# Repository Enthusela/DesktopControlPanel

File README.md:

# The Desktop Control Panel Project

An open-source, hand-built, tactile, home-brew smart-home hub with analog PC audio monitoring and control.

## Features

* ARGB LED device control with HSV and color-temperature control modes
* App-based volume mixing in Windows, including OS/Game/Discord channels
* Motorised knobs enable multiple control modes on a single set of inputs
* Mains power control: Toggle switches control mains power to the PC, monitors, and speakers via rental-safe RF-based remote-control mains outlets.
* Analog audio monitoring: PC soundcard connects to VU meters and IN-9 Nixie Tubes for level and 3-band spectrum monitoring, respectively
* Moog-inspired build quality: wood cabinet, black brushed-aluminium faceplate, big, satisfying switchgear, and actual Moog knobs/rockers because why not.
* "Seamless" E-ink display: White-on-black E-ink panel creates a non-light-emitting display integrated into the non-light-emitting faceplate.
* Integrated website: the website for this Control Panel project is hosted on the Raspberry Pi running inside the Control Panel
* Integration with Home Assistant for ARGB room-lighting via ESP Wifi boards
* Automatic Temperature-based color control: automatically transition room lighting from cool to warm as the sun sets here in Perth, Western Australia.
* Homebrew phone-control app: Home Assistant has this, of course, but this sounded like a good excuse to learn React Native.

<details>
<summary>Feature Development Status Table</summary>

| Feature/Pipeline                      | Order In Pipeline | Sub-function                        | Status |
|:--------------------------------------|:---:|:----------------------------------------------------|:-----|
| Faceplate -> Mega Hardware Pipeline   | 1   | Faceplate Input Hardware                            | Done |
| Faceplate -> Mega Hardware Pipeline   | 2   | Faceplate Input Breakout Board                      | Testing |
| Faceplate -> Mega Hardware Pipeline   | 3   | Mega* Input Shield                                  | Testing |
| Mega -> Raspi Hardware Pipeline       | 1   | USB Connection                                      | Done |
| Raspi -> Uno Hardware Pipeline        | 1   | USB Connection                                      | Done |
| Raspi -> PC Hardware Pipeline         | 1   | Local Wifi Connection                               | Done |
| Input Knob Motorisation               | 1   | Mega Programming - Input Knob Control Modes         | Done |
| Input Knob Motorisation               | 2   | Motor Driver Shield                                 | Done |
| Input Knob Motorisation               | 3   | Shield -> Motor Connection                          | Done | 
| PC ARGB Control                       | 1   | Mega Programming - Input signal processing          | Done |
| PC ARGB Control                       | 2a  | Raspi* Programming - Input passthrough to Uno       | Done |
| PC ARGB Control                       | 2b  | Raspi Programming - Home Assistant/Web App          | Not Started |
| PC ARGB Control                       | 3a  | Uno* Programming - Manual HSV-based Color Control   | Done |
| PC ARGB Control                       | 3b  | Uno Programming - Manual Temp-based Color Control   | Done |
| PC ARGB Control                       | 3c  | Uno Programming - Auto Temp-based Color Control     | Not Started |
| PC ARGB Control                       | 4   | Uno ARGB Breakout Shield                            | To Be Ordered |
| PC ARGB Control                       | 5   | PC ARGB Devices                                     | Done |
| PC Volume Control                     | 1   | Raspi Programming - Input passthrough to PC         | Done |
| PC Volume Control                     | 2a  | PC Programming - Main Volume Control                | Done |
| PC Volume Control                     | 2b  | PC Programming - Three-channel App Volume Control   | Done |
| PC Volume Control                     | 2c  | PC Programming - Audio Output Device Selection      | Done |
| Mains Power Control                   | 1   | Mega Programming - Input Signal Processing          | In progress |
| Mains Power Control                   | 2   | Mega -> RF PCB Breakout Board                       | In progress |
| Mains Power Control                   | 3   | RF PCB -> Remote Mains Outlet Connection            | In progress |
| Mains Power Control                   | 4   | Remote Mains Outlets - Test Working                 | In progress |
| PC Audio Level Meters                 | 1   | Soundcard TRS Output Levels                         | Done |
| PC Audio Level Meters                 | 2a  | Soundcard -> Driver Board Connection                | Done |
| PC Audio Level Meters                 | 2b  | Power Supply -> Driver Board Connection             | Developing |
| PC Audio Level Meters                 | 3   | VU Meter Driver Board                               | Done |
| PC Audio Level Meters                 | 4a  | VU Meter Level Outputs                              | Done |
| PC Audio Level Meters                 | 4b  | VU Meter LED Outputs                                | Done |
| PC Audio Level Meters                 | 5a  | VU Meters                                           | Done |
| PC Audio Level Meters                 | 5b  | VU Meter LEDs                                       | Prototyped |
| PC Audio Spectrum Analyser            | 1   | Soundcard Optical Output Levels                     | Done |
| PC Audio Spectrum Analyser            | 2   | Soundcard -> Digital I/O Board Connection           | Done |
| PC Audio Spectrum Analyser            | 3   | Raspberry Pi Digital Audio I/O Board                | Testing |
| PC Audio Spectrum Analyser            | 4   | Raspberry Pi Digital Audio I/O Processing           | Developing |
| PC Audio Spectrum Analyser            | 5   | Custom Nixie Tube Driver HAT                        | Developing |
| PC Audio Spectrum Analyser            | 6   | Driver HAT -> Nixie Tube Connection                 | Done |
| PC Audio Spectrum Analyser            | 7   | Power Supply to Driver Board                        | Developing |
| e-Ink Display                         | 1   | Raspberry Pi Programming - Image Output             | Developing |
| e-Ink Display                         | 2   | Raspberry Pi HAT                                    | Done |
| e-Ink Display                         | 3   | e-Ink Display                                       | Done |
| Project Website                       | 1   | Proxy Server (nginx)                                | Done |
| Project Website                       | 2   | Domain Hosting                                      | Done |
| Project Website                       | 3   | Server (node.js)                                    | Done |
| Project Website                       | 4a  | Homepage                                            | In progress |
| Project Website                       | 4b  | Brief                                               | In progress |
| Project Website                       | 4c  | Timeline                                            | In progress |
| Project Website                       | 4d  | Parts List                                          | In progress |
| Project Website                       | 4e  | Gallery                                             | In progress |
| Project Website                       | 4f  | Interactive Panel Map                               | Not started |
| Cabinet                               | N/A | Faceplate VU Meter Mounts                           | Done |
| Cabinet                               | N/A | Faceplate Nixie Tube Mounts                         | Done |
| Cabinet                               | N/A | Faceplate Soundcard Mount                           | Done |
| Cabinet                               | N/A | Faceplate e-Ink Display Mount                       | Done |
| Cabinet                               | N/A | Faceplate Input Knobs                               | Done |
| Cabinet                               | N/A | Faceplate Input Knob Motors/Gears                   | Done |
| Cabinet                               | N/A | Faceplate Input Rocker Switches                     | Done |
| Cabinet                               | N/A | Faceplate Input Toggle Switches                     | Done |
| Cabinet                               | N/A | Faceplate Input Push-button Switches                | Done |
| Cabinet                               | N/A | Internal Mounting Plate                             | Done |
| Cabinet                               | N/A | Rear Plate Plate                                    | Done |
| Cabinet                               | N/A | Cabinet Top Plate                                   | Done |
| Cabinet                               | N/A | Cabinet Side Plates                                 | Done |
| Cabinet                               | N/A | Cabinet Bottom Plate                                | In progress |
| Room ARGB Control                     | 1a  | Raspi Programming - Home Assistant Server           | Not started |
| Room ARGB Control                     | 1b  | Raspi Programming - Home Assistant Phone App        | Not started |
| Room ARGB Control                     | 2   | ESP32 Programming - Home Assistant Client           | Not started |
| Room ARGB Control                     | 3   | ESP32 ARGB Breakout Shield                          | Prototyped  |
| Room ARGB Control                     | 4   | Room ARGB Devices - Confirm Working                 | Not started |
| e-Ink Touch Overlay                   | 1   | Touch Overlay                                       | Not started |
| e-Ink Touch Overlay                   | 2   | Touch Overlay -> Raspi Connection                   | Not started |

* "Mega", "Raspi", and "Uno" refer to the Arduino Mega, Raspberry Pi, and Arduino Uno boards used, respectively.

</details>

## Background

This project grew out of a number of frustrations I was having building a killer PC setup that was both functional and aesthetically-pleasing: both important in a 1-by-1 apartment where said PC setup takes up a good third of the available living-room space.

<details>
<summary>ARGB controller software is not pleasant to use</summary>
<br>
The main idea for this project came out of my own frustration with existing hardware/software for controlling ARGB LEDs built into PC components. Most ARGB devices, like fans, must be plugged into a controller that interfaces with software running on the PC. This software is manufacturer-specific, closed-source, and typically quite limited in what it can do: you get some pre-loaded color patterns, but if you want it to do anything else, you're out of luck. To make matters worse, the software is often classic "bloatware": it insists on starting on login, then runs slow, chews up computer resources on functions you didn't ask for, and crashes often. Factor in multiple apps running for different manufacturers, and the user experience gets frustrating fast. While there is some scope to synchronise lighting across different manufacturer's products, these aren't ideal either: I was able to sync my CoolerMaster fans and my Corsair mouse, for instance, but only by using ARGB software tied to my motherboard, which was more limited than the software that came with either product.
</details> 

<details>
<summary>ARGB controller hardware is not special</summary>
<br>
Despite these software problems, I noticed that the physical connections across all my devices was using the same three-pin standard. A quick internet search taught me that the standard was, as expected, a simple Vcc-Data-Gnd pin layout.
</details>

<details>
<summary>Humans did not evolve to relax under rainbow lighting</summary>
<br>
While thinking about making my own ARGB controller, one feature that I particularly wanted was temperature-based color control. I liked the idea of room lighting that could change from cool white during the day to very warm, basically orange, at night. Ideally I'd have my whole apartment lit up like this to make it a well-lit space during the day that gradually becomes softer, warmer, and hopefully more sleep-conducive at night. This is pretty much the antithesis of most pre-built ARGB options, whether that's PC components or ARGB strip-lighting with controllers, which default to "rainbow vomit cyclone". Of course, if I had my own controller then I could make my color-temperature dreams come true.
</details>

<details>
<summary>I like my hardware ~ t e x t u r a l ~</summary>
<br>
I don't know about you, but I really love old-school electronics hardware, particularly audio hardware like synthesisers, amps, mixing tables, etc. The use of materials like wood and metal and glass makes them look and feel so much nicer, so much more hand-crafted, than anything you can get out of molded plastic. All that physical switchgear gives it a sense of weight and purpose; you just know there's a heap of clever analog wizardry going on in there as you move physical components about. It's kind of the opposite of the experience I was getting with the ARGB controllers, which is basically "plug in this small plastic box and hope the software will work". If I was ever going to build my own electronics hardware, something really cool, it would take a lot of design queues from that kind of old-school equipment.
</details>

<details>
<summary>I wanted a new job</summary>
<br>
This project became part of my Master Plan to pivot from Mechatronics Engineer to Software Engineer. If everything so far sounds like something I could have just bought one or more smart-home products to do, then yes, you're right, but as the feature set grew I realised varied tech stack required to build it would make it an ideal showcase project.
</details>

<details>
<summary>The Idea</summary>
<br>
So I have lighting software that doesn't work, connected to hardware that isn't complicated, pushing out colors I don't like, in a form factor that's the opposite of what I like in technology. What if I made the opposite of that? An open-source controller, accepting whatever standard plug-ins my devices used, with all of the color-control options I could think up, built into a sleek bit of hardware that makes you go "Nice." Maybe it'd look a little like this...
<br>

This repo contains (almost) everything I've built so far to make bring that digital finger-painting to life.
</details>

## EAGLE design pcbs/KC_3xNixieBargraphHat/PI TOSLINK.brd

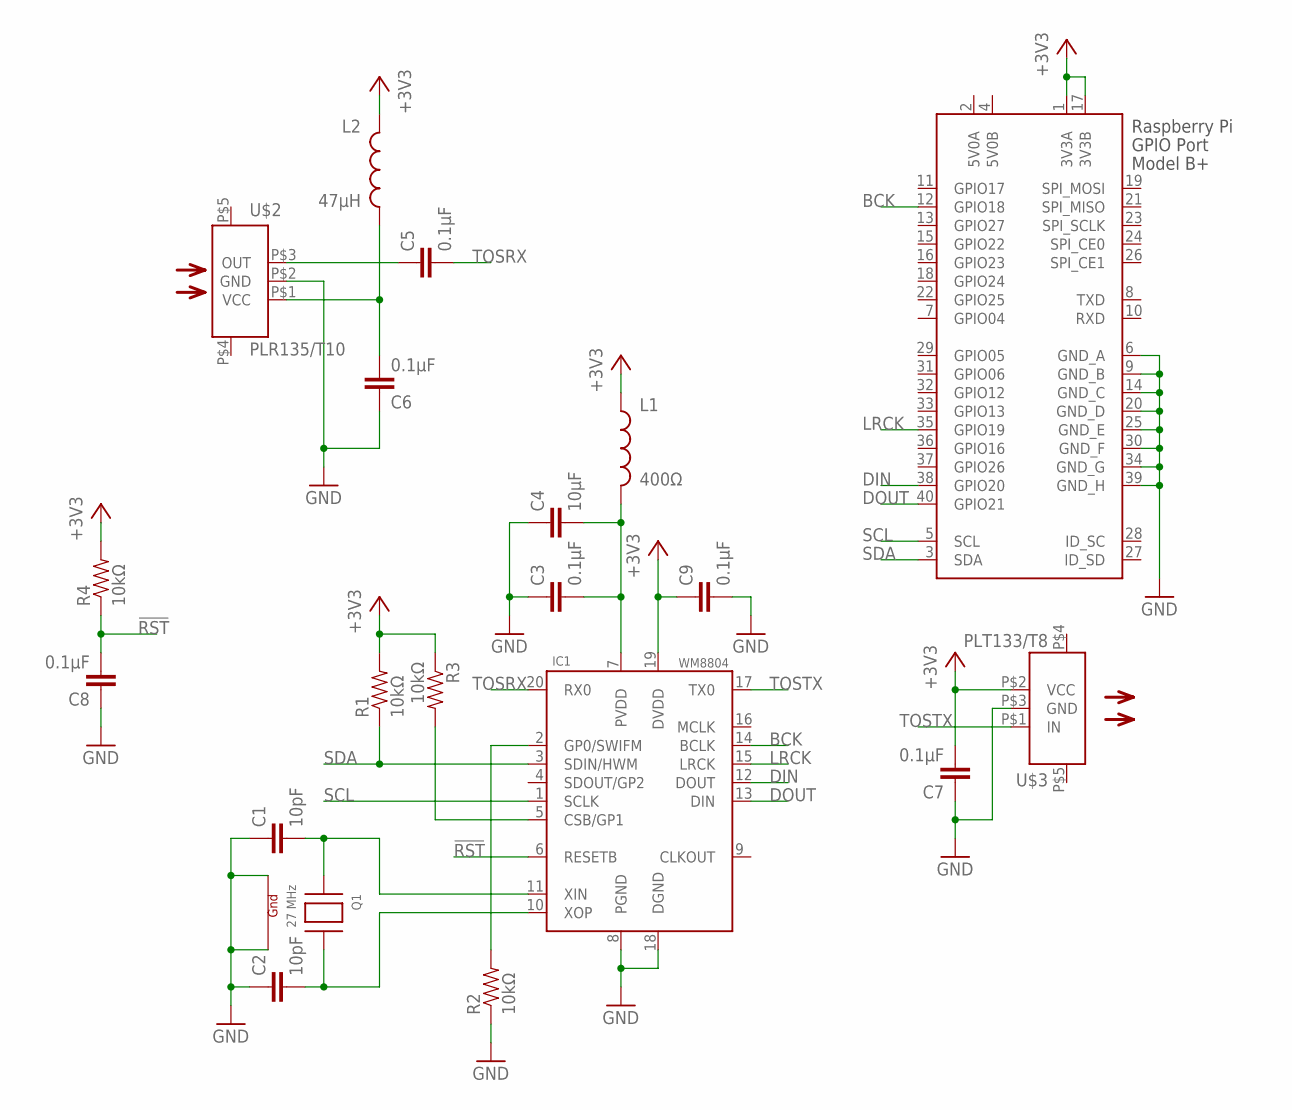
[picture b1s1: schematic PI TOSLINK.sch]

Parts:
C1, C2: 10pF; 0805
C3, C5, C6, C7, C8, C9: 0.1µF; 0805
C4: 10µF; 0805
IC1: WM8804; SSOP20BU
L1: 400Ω; 0805
L2: 47µH; 0805
Q1: 27 MHz; NX3225
R1, R2, R3, R4: 10kΩ; 0805
U$2: PLR135/T10
U$3: PLT133/T8; PLR135/T10
X1: RASPI_GPIO_B+#_PIN; RASPI_GPIO_B+_PIN

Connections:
5V0A: X1.2 (5V0A)
5V0B: X1.4 (5V0B)
!RST: C8.2, IC1.6 (RESETB), R4.1
+3V3: C7.2, C9.1, IC1.19 (DVDD), L1.1, L2.1, R1.2, R3.1, R4.2, U$3.P$2 (VCC), X1.1 (3V3A), X1.17 (3V3B)
BCK: IC1.14 (BCLK), X1.12 (GPIO18)
DIN: IC1.12 (DOUT), X1.38 (GPIO20)
DOUT: IC1.13 (DIN), X1.40 (GPIO21)
GND: C1.1, C2.1, C3.1, C4.1, C6.1, C7.1, C8.1, C9.2, IC1.8 (PGND), IC1.18 (DGND), Q1.2 (G2), Q1.4 (G1), R2.1, U$2.P$2 (GND), U$3.P$3 (GND), X1.6 (GND_A), X1.9 (GND_B), X1.14 (GND_C), X1.20 (GND_D), X1.25 (GND_E), X1.30 (GND_F), X1.34 (GND_G), X1.39 (GND_H)
LRCK: IC1.15 (LRCK), X1.35 (GPIO19)
unnamed: C2.2, IC1.10 (XOP), Q1.3 (X2)
unnamed: C1.2, IC1.11 (XIN), Q1.1 (X1)
unnamed: C5.1, U$2.P$3 (OUT)
unnamed: IC1.2 (GP0/SWIFM), R2.2
unnamed: IC1.5 (CSB/GP1), R3.2
unnamed: C3.2, C4.2, IC1.7 (PVDD), L1.2
unnamed: C6.2, L2.2, U$2.P$1 (VCC)
SCL: IC1.1 (SCLK), X1.5 (SCL)
SDA: IC1.3 (SDIN/HWM), R1.1, X1.3 (SDA)
TOSRX: C5.2, IC1.20 (RX0)
TOSTX: IC1.17 (TX0), U$3.P$1 (IN)

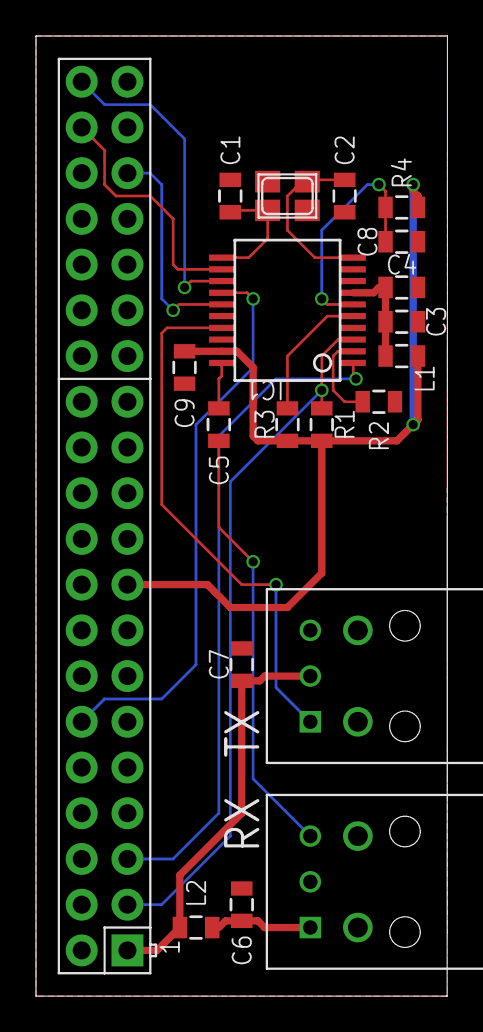
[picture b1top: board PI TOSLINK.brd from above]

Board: 2 copper layers, 22.9 x 53.3 mm, 20 parts (0 on the bottom side), 18 nets.

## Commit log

2023-02-07 Initial commit. Running homepage pset website on local flask.
2023-02-16 Uploaded working files from Raspberry Pi. Webpage is ready for hosting.
2023-02-16 Added app.py and templates folder to staged changes.
2023-02-17 Added package-json files
2023-02-17 Added wordclock e-ink test code
2023-02-17 Added e-ink display wordclock test
2023-02-17 Converted wordclock from folder to submodule
2023-02-17 Updated wordclock files
2023-02-17 Untracked e-ink img folders
2023-02-17 Removed wordclock sub-module
2023-02-17 Added files from successful 7-color e-ink tests
2023-03-16 Bulk commit.
2023-03-17 Added motorised takeover
2023-04-01 Improved timeline. Began converting to node.js.
2023-04-07 Updated Timeline with dynamic thumbnail rendering
2023-10-16 Bulk pre-portfolio commit
2023-10-16 Added missing /audio files
    The original three files appear to be test recordings: the rest were stored in the DCP repo, I believe to save space on my Raspberry Pi, which I now see is unnecessary.
2023-10-16 Merged py folders for PC and raspi
    Raspi scripts for arduino/pc comms and PC scripts for raspi comms/volume control have been merged into one py directory.
2023-10-16 Merged transcript files
    Existing test transcript files have been merged with the complete set from DesktopControlPanel, which were used to generate the content for the website project timeline.
2023-10-16 Added ESPWifiARGBControl code from offline repo
    This logic was developed offline by mistake briefly, and is now being merged into the main repo
2023-10-16 Added RF test code from offline repo
    This logic was tested offline by mistake briefly, and is now being merged into the online repo
2023-10-16 Added archival pre-GitHub files
    These files are earlier versions of code that was eventually duplicated onto github. They appear to be snippets of test code that was later incorporated into "official" code versions at the creation 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
2023-10-16 Added pcbs directory
    Added new directory for the PCB dev files (mostly kicad files)
2023-10-16 Create faceplate directory
    Added faceplate directory as start of move to functionality-based organisation: previously organisation was language-based, which is helpful for code dev work but not so much for hardware.
2023-10-16 Create cabinet dir as root for hardware files
    Created cabinet dir and moved faceplate inside. Added folders for existing dwg and f3d files
2023-10-18 Updated js_test dir to eink
2023-10-18 Updates to dir names, added .gitignore
    Moved "js_test" to "eink" dir after review of contents. Added .gitignore, added KiCad backup dirs to ignore list.
2023-10-18 Reorganised folders based on hardware components
2023-10-18 Reorganised resources for website
    Resources for the website were spread across multiple folders in the root directory: these have now been reconciled in the "website" directory to distinguish them further from the other components of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
    The folders appear to contain duplicate files that will be reconciled in the next commit.
2023-10-18 Consolidated img files in website folder
2023-10-18 Consolidated "AI Journalling" files in website dir
2023-10-18 Relocated eink-only "sh" dir to "eink" dir
2023-10-18 Reorganised "py" dir into relevant feature dirs
2023-10-18 Relocated argb web app files, removed archive dir
    Files from the original web-app test for ARGB control were found in the archive dir: the remaining files were confirmed to be redundant and/or outdated and safe for deletion. This should be the last 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
2023-10-18 Removed audio journal files
    Removed the original audio files from the ai_journal folder as these made up half the size of the repo despite already being transcribed.
2023-10-18 Updated .gitignore
2023-10-18 nodejs now generates img thumbs on server start
2023-10-18 Gallery uses hires in lightbox, otherwise thumbs
2023-10-18 Added missing images to public/images folder
2023-10-19 Renamed website/js to website/node
2023-10-19 Deleted HTML-only web page templates dir
2023-10-19 Added feature_status table
2023-11-30 Progressed to Ivy-focused analysis
    Progressed FitBit feature first analysis. Landed on a different method to analyse the features of the Ivy one by one and relate back to the FitBit features, rather than the other way round.
2025-11-09 Containerised argb_ctrl web app for dev on PC
2025-11-09 Added docker files
2025-11-10 Got ARGB working again. Added test script using uv
2025-11-10 Reorganised argb-test code
2025-11-10 Web app ui now updates values correctly
2026-01-31 Push before reinstalling

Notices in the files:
parts and their libraries:
SparkFun-Capacitors: Licensing: CC v3.0 Share-Alike You are welcome to use this library for commercial purposes.
